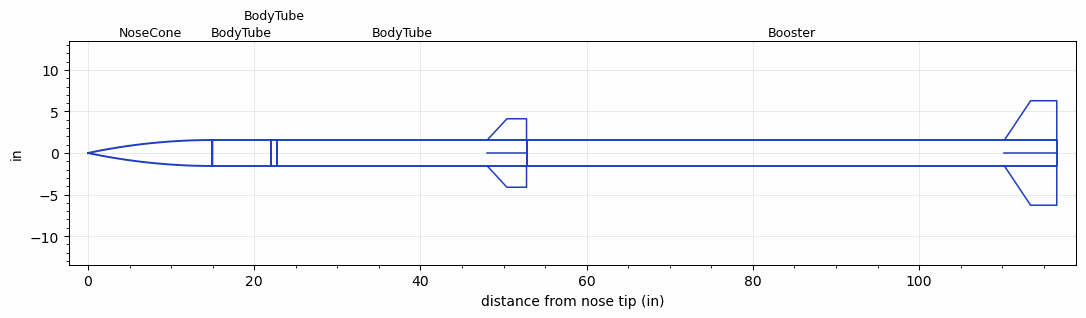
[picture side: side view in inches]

<RASAeroDocument>
 <FileVersion>2</FileVersion>
 <RocketDesign>
  <NoseCone>
   <Length>14.96063</Length>
   <Diameter>3.12</Diameter>
   <Shape>Tangent Ogive</Shape>
   <Location>0</Location>
  </NoseCone>
  <BodyTube>
   <Length>7</Length>
   <Diameter>3.12</Diameter>
   <Location>14.96063</Location>
  </BodyTube>
  <BodyTube>
   <Length>0.8</Length>
   <Diameter>3.12</Diameter>
   <Location>21.96063</Location>
  </BodyTube>
  <BodyTube>
   <Length>30</Length>
   <Diameter>3.12</Diameter>
   <Location>22.76063</Location>
   <Fin>
    <Count>4</Count>
    <Chord>4.7244</Chord>
    <Span>2.5591</Span>
    <SweepDistance>2.3622</SweepDistance>
    <TipChord>2.3622</TipChord>
    <Thickness>0.2756</Thickness>
    <Location>4.7244</Location>
    <AirfoilSection>Square</AirfoilSection>
   </Fin>
  </BodyTube>
  <Booster>
   <Length>63.8</Length>
   <Diameter>3.12</Diameter>
   <InsideDiameter>3.12</InsideDiameter>
   <Location>52.76063</Location>
   <ShoulderLength>0</ShoulderLength>
   <Fin>
    <Count>4</Count>
    <Chord>6.299212</Chord>
    <Span>4.72441</Span>
    <SweepDistance>3.149606</SweepDistance>
    <TipChord>3.149606</TipChord>
    <Thickness>0.2755905</Thickness>
    <Location>6.299212</Location>
    <AirfoilSection>Square</AirfoilSection>
   </Fin>
  </Booster>
  <Surface>Smooth (Zero Roughness)</Surface>
  <ModifiedBarrowman>False</ModifiedBarrowman>
  <Turbulence>False</Turbulence>
  <Booster1Nozzle>2.75</Booster1Nozzle>
  <UseBooster1>True</UseBooster1>
  <UseBooster2>False</UseBooster2>
 </RocketDesign>
 <LaunchSite>
  <Altitude>0</Altitude>
  <Pressure>0</Pressure>
  <RodAngle>0</RodAngle>
  <RodLength>10</RodLength>
  <Temperature>74</Temperature>
  <WindSpeed>20</WindSpeed>
 </LaunchSite>
 <Recovery>
  <Altitude1>1000</Altitude1>
  <Altitude2>1000</Altitude2>
  <DeviceType1>Parachute</DeviceType1>
  <DeviceType2>None</DeviceType2>
  <Event1>True</Event1>
  <Event2>False</Event2>
  <Size1>0.5</Size1>
  <Size2>1</Size2>
  <EventType1>Apogee</EventType1>
  <EventType2>None</EventType2>
  <CD1>0.5</CD1>
  <CD2>1.33</CD2>
 </Recovery>
 <SimulationList>
  <Simulation>
   <SustainerEngine>Dart  (NoThrust)</SustainerEngine>
   <SustainerLaunchWt>8.3</SustainerLaunchWt>
   <SustainerCG>32.56</SustainerCG>
   <SustainerIgnitionDelay>0</SustainerIgnitionDelay>
   <Booster1Engine>L2200G  (AT)</Booster1Engine>
   <Booster1LaunchWt>27.63</Booster1LaunchWt>
   <Booster1SeparationDelay>0</Booster1SeparationDelay>
   <Booster1IgnitionDelay>0</Booster1IgnitionDelay>
   <Booster1CG>76.77</Booster1CG>
   <Booster1NozzleDiameter>2.965</Booster1NozzleDiameter>
   <IncludeBooster1>True</IncludeBooster1>
   <Booster2Delay>0</Booster2Delay>
   <IncludeBooster2>False</IncludeBooster2>
   <TimetoApogee>18.51027</TimetoApogee>
   <MaxAltitude>7521.37</MaxAltitude>
   <MaxVelocity>1102.735</MaxVelocity>
   <OptimumWt>13.695</OptimumWt>
   <OptimumMaxAlt>13.695</OptimumMaxAlt>
  </Simulation>
 </SimulationList>
</RASAeroDocument>
